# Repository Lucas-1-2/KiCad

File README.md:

# Raccolta di schematici e progettazioni PCB mediante KiCad

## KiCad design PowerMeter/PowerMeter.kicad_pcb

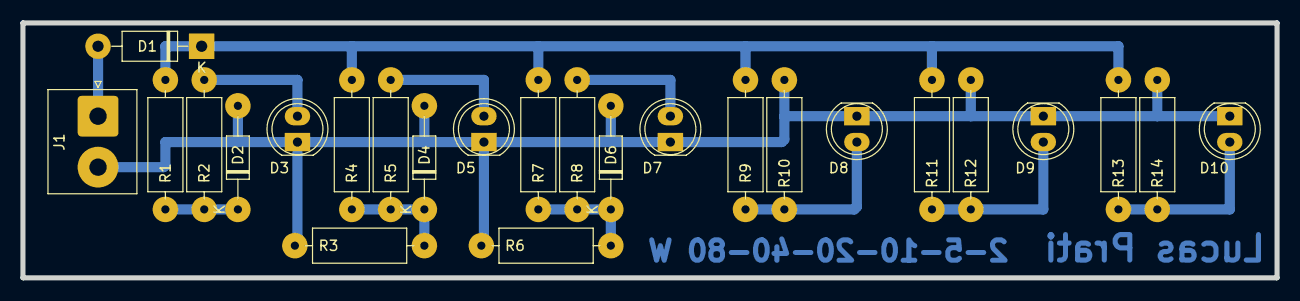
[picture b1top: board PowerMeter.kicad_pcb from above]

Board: 2 copper layers, 123.0 x 25.0 mm, 25 parts (0 on the bottom side), 12 nets.

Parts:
D1: 1N4004; D_DO-41_SOD81_P10.16mm_Horizontal
D2, D4, D6: 2,7V 500mW BZX79C2V7; D_DO-35_SOD27_P10.16mm_Horizontal
D3, D5, D7, D8, D9, D10: LED; LED_D5.0mm
J1: Conn_01x02_Male; JST_NV_B02P-NV_1x02_P5.00mm_Vertical
R1, R3: 220; R_Axial_DIN0309_L9.0mm_D3.2mm_P12.70mm_Horizontal
R2, R5, R6, R8, R10, R12, R14: 100; R_Axial_DIN0309_L9.0mm_D3.2mm_P12.70mm_Horizontal
R4, R7: 330; R_Axial_DIN0309_L9.0mm_D3.2mm_P12.70mm_Horizontal
R9: 560; R_Axial_DIN0309_L9.0mm_D3.2mm_P12.70mm_Horizontal
R11: 820; R_Axial_DIN0309_L9.0mm_D3.2mm_P12.70mm_Horizontal
R13: 1k2; R_Axial_DIN0309_L9.0mm_D3.2mm_P12.70mm_Horizontal

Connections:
GND: D2.2, D3.1, D4.2, D5.1, D6.2, D7.1, D8.1, D9.1, D10.1, J1.2, R3.2, R6.2, R10.2, R12.2, R14.2
unnamed: D1.1, R1.1, R4.1, R7.1, R9.1, R11.1, R13.1
unnamed: D2.1, R1.2, R2.2
unnamed: D3.2, R2.1
unnamed: D4.1, R3.1, R4.2, R5.2
unnamed: D5.2, R5.1
unnamed: D6.1, R6.1, R7.2, R8.2
unnamed: D7.2, R8.1
unnamed: D8.2, R9.2, R10.1
unnamed: D9.2, R11.2, R12.1
unnamed: D10.2, R13.2, R14.1
VCC: D1.2, J1.1

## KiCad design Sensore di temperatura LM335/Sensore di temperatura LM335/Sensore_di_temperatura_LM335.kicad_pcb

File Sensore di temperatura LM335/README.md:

# Progetto sensore di temperatura con LM335

**TPSEE; A.S. 2022/23, ITT G.Marconi - Forlì.**

- **Team**: Lucas Prati, Yassir El Kacimi
- **Docente**: prof. Samuele Mazzolini

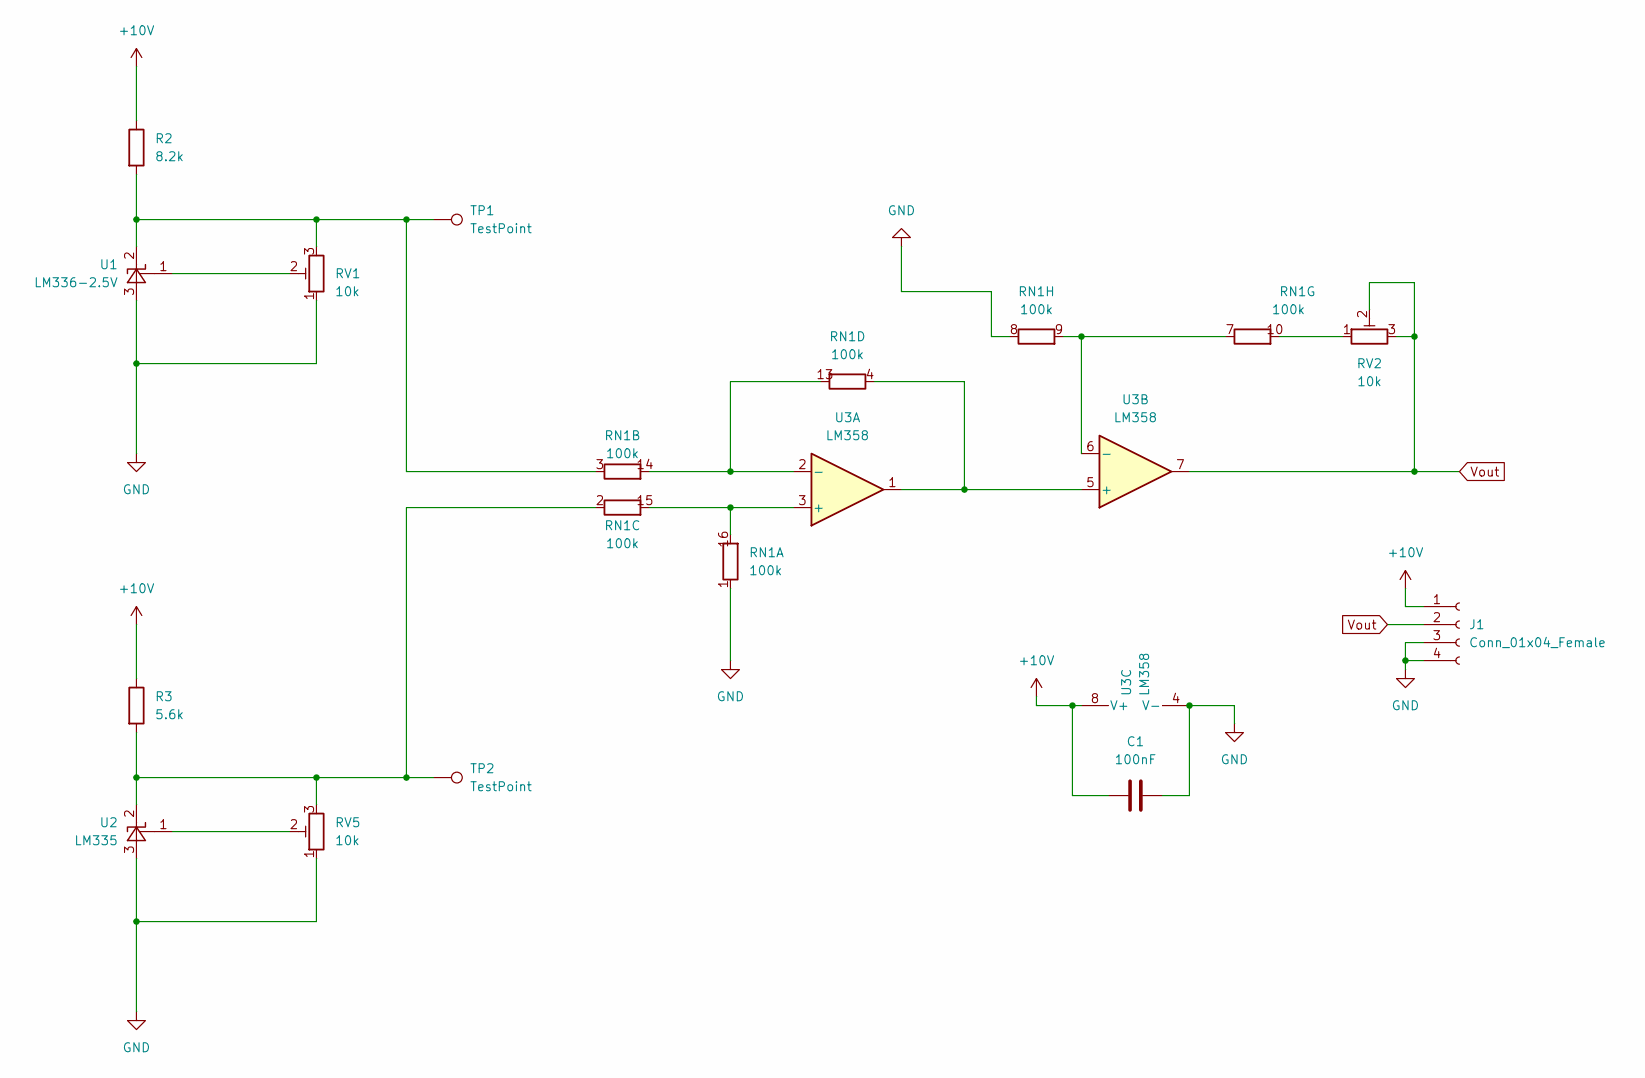
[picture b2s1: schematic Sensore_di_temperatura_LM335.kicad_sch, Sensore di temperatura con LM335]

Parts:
C1: 100nF; C_Rect_L7.0mm_W2.5mm_P5.00mm
J1: Conn_01x04_Female; TerminalBlock_Phoenix_MKDS-1,5-4_1x04_P5.00mm_Horizontal
R2: 8.2k; R_Axial_DIN0309_L9.0mm_D3.2mm_P12.70mm_Horizontal
R3: 5.6k; R_Axial_DIN0309_L9.0mm_D3.2mm_P12.70mm_Horizontal
RN1: 100k; DIP-16_W7.62mm_LongPads
RV1, RV2, RV5: 10k; Potentiometer_Bourns_3339P_Vertical
TP1, TP2: TestPoint; PinHeader_1x01_P2.00mm_Vertical
U1: LM336-2.5V; TO-92_Wide
U2: LM335; TO-92_Wide
U3: LM358; DIP-8_W7.62mm_LongPads

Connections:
+10V: C1.1, J1.1, R2.1, R3.1, U3.8 (V+)
GND: C1.2, J1.3, J1.4, RN1.1 (R1.1), RN1.8 (R8.1), RV1.1, RV5.1, U1.3 (A), U2.3 (A), U3.4 (V-)
unnamed: R2.2, RN1.3 (R3.1), RV1.3, TP1.1, U1.2 (K)
unnamed: R3.2, RN1.2 (R2.1), RV5.3, TP2.1, U2.2 (K)
unnamed: RN1.4 (R4.1), U3.1, U3.5 (+)
unnamed: RN1.7 (R7.1), RN1.9 (R8.2), U3.6 (-)
unnamed: RN1.10 (R7.2), RV2.1
unnamed: RN1.13 (R4.2), RN1.14 (R3.2), U3.2 (-)
unnamed: RN1.15 (R2.2), RN1.16 (R1.2), U3.3 (+)
unnamed: RV1.2, U1.1 (FB)
unnamed: RV5.2, U2.1 (FB)
Vout: J1.2, RV2.2, RV2.3, U3.7

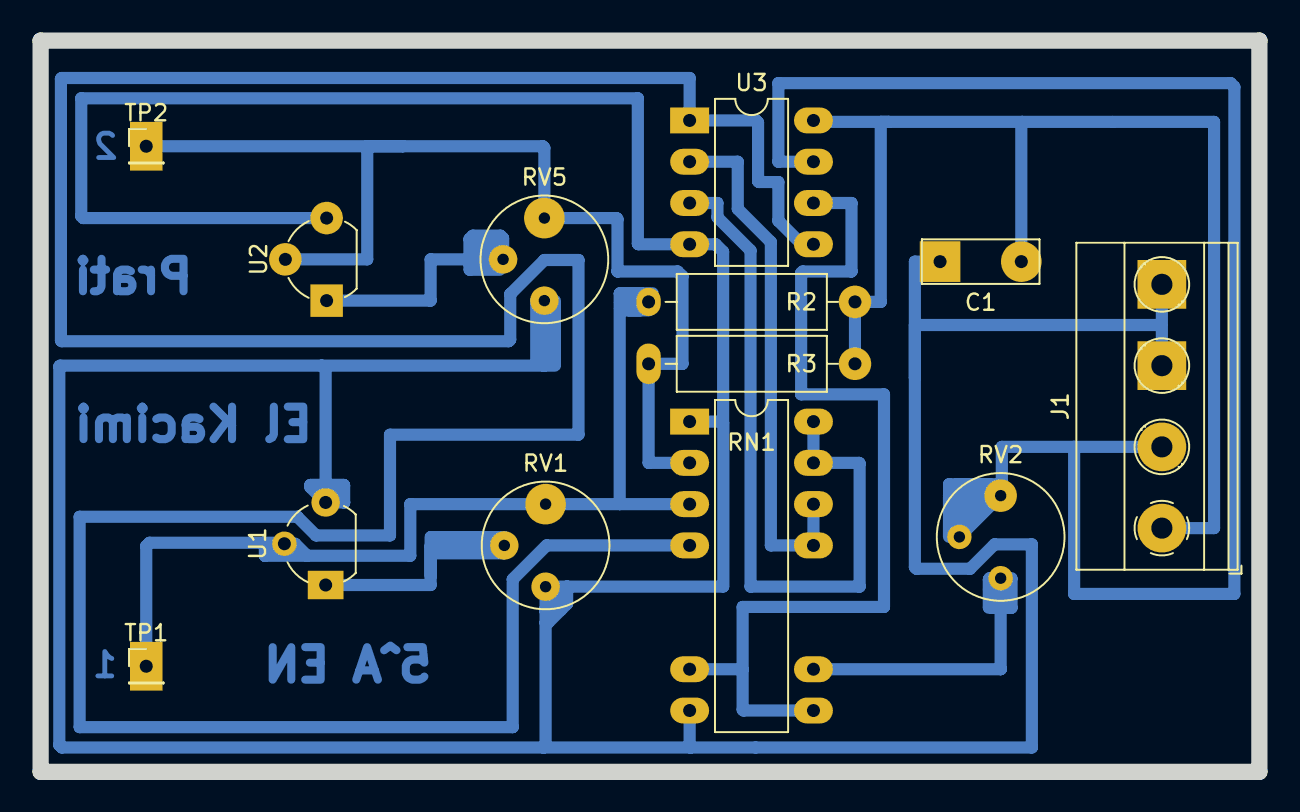
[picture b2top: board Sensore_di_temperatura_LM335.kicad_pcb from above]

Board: 2 copper layers, 75.0 x 45.0 mm, 13 parts (0 on the bottom side), 12 nets.

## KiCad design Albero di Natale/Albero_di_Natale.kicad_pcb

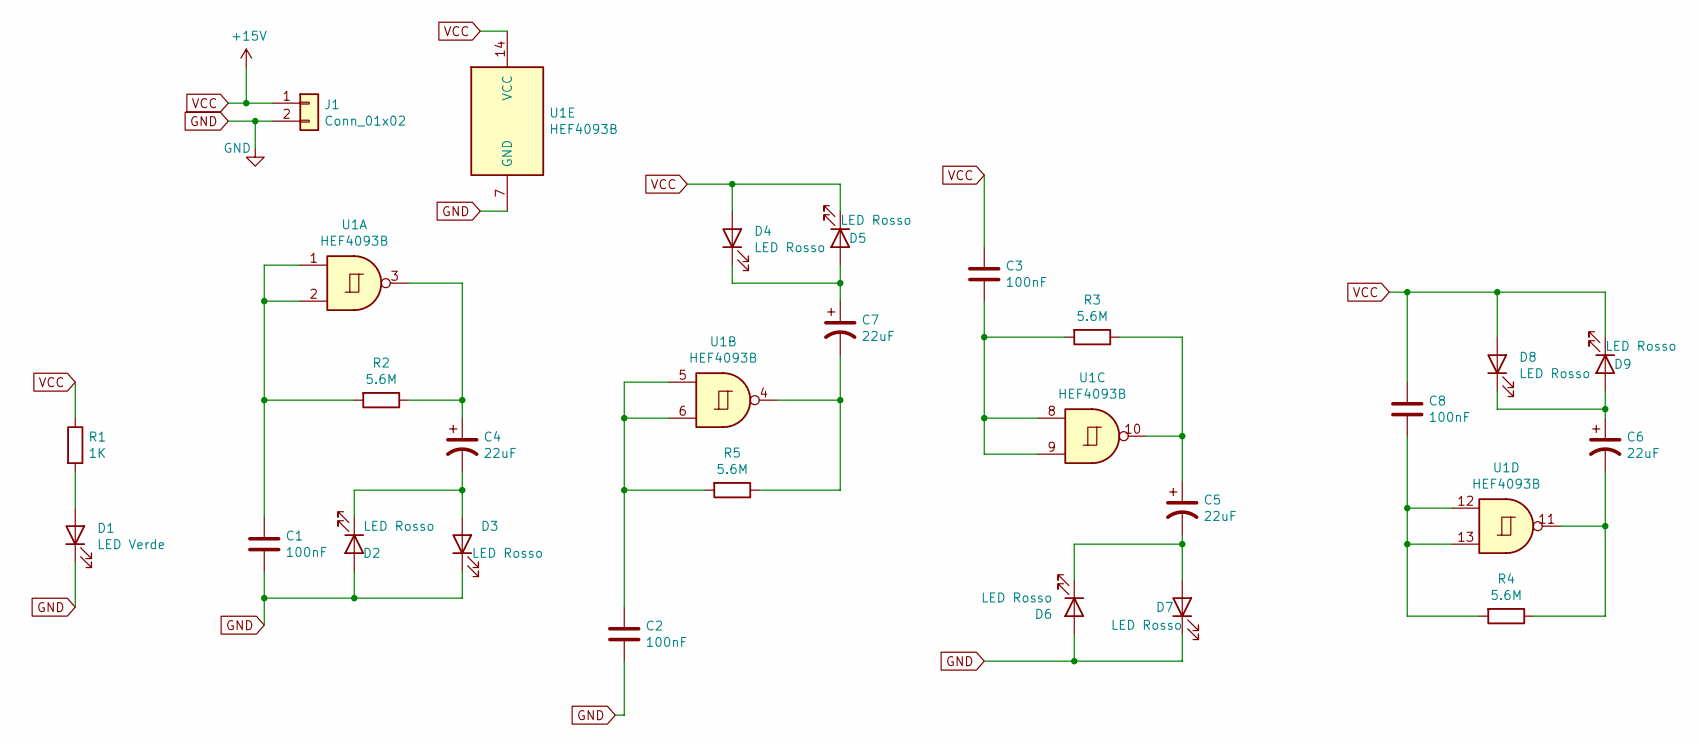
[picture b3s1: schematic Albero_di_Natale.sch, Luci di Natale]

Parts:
C1, C2, C3, C8: 100nF; C_Disc_D3.8mm_W2.6mm_P2.50mm
C4, C5, C6, C7: 22uF; C_Radial_D6.3mm_H5.0mm_P2.50mm
D1: LED Verde; LED_D5.0mm
D2, D3, D4, D5, D6, D7, D8, D9: LED Rosso; LED_D5.0mm
J1: Conn_01x02; JST_NV_B02P-NV_1x02_P5.00mm_Vertical
R1: 1K; R_Axial_DIN0309_L9.0mm_D3.2mm_P12.70mm_Horizontal
R2, R3, R4, R5: 5.6M; R_Axial_DIN0309_L9.0mm_D3.2mm_P12.70mm_Horizontal
U1: HEF4093B; DIP-14_W7.62mm_LongPads

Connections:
GND: C1.2, C2.2, D1.1 (K), D2.2 (A), D3.1 (K), D6.2 (A), D7.1 (K), J1.2, U1.7 (GND)
unnamed: C1.1, R2.2, U1.1, U1.2
unnamed: C2.1, R5.2, U1.5, U1.6
unnamed: C3.2, R3.2, U1.8, U1.9
unnamed: C4.1, R2.1, U1.3
unnamed: C4.2, D2.1 (K), D3.2 (A)
unnamed: C5.1, R3.1, U1.10
unnamed: C5.2, D6.1 (K), D7.2 (A)
unnamed: C6.1, D8.1 (K), D9.2 (A)
unnamed: C6.2, R4.1, U1.11
unnamed: C7.1, D4.1 (K), D5.2 (A)
unnamed: C7.2, R5.1, U1.4
unnamed: C8.2, R4.2, U1.12, U1.13
unnamed: D1.2 (A), R1.2
VCC: C3.1, C8.1, D4.2 (A), D5.1 (K), D8.2 (A), D9.1 (K), J1.1, R1.1, U1.14 (VCC)

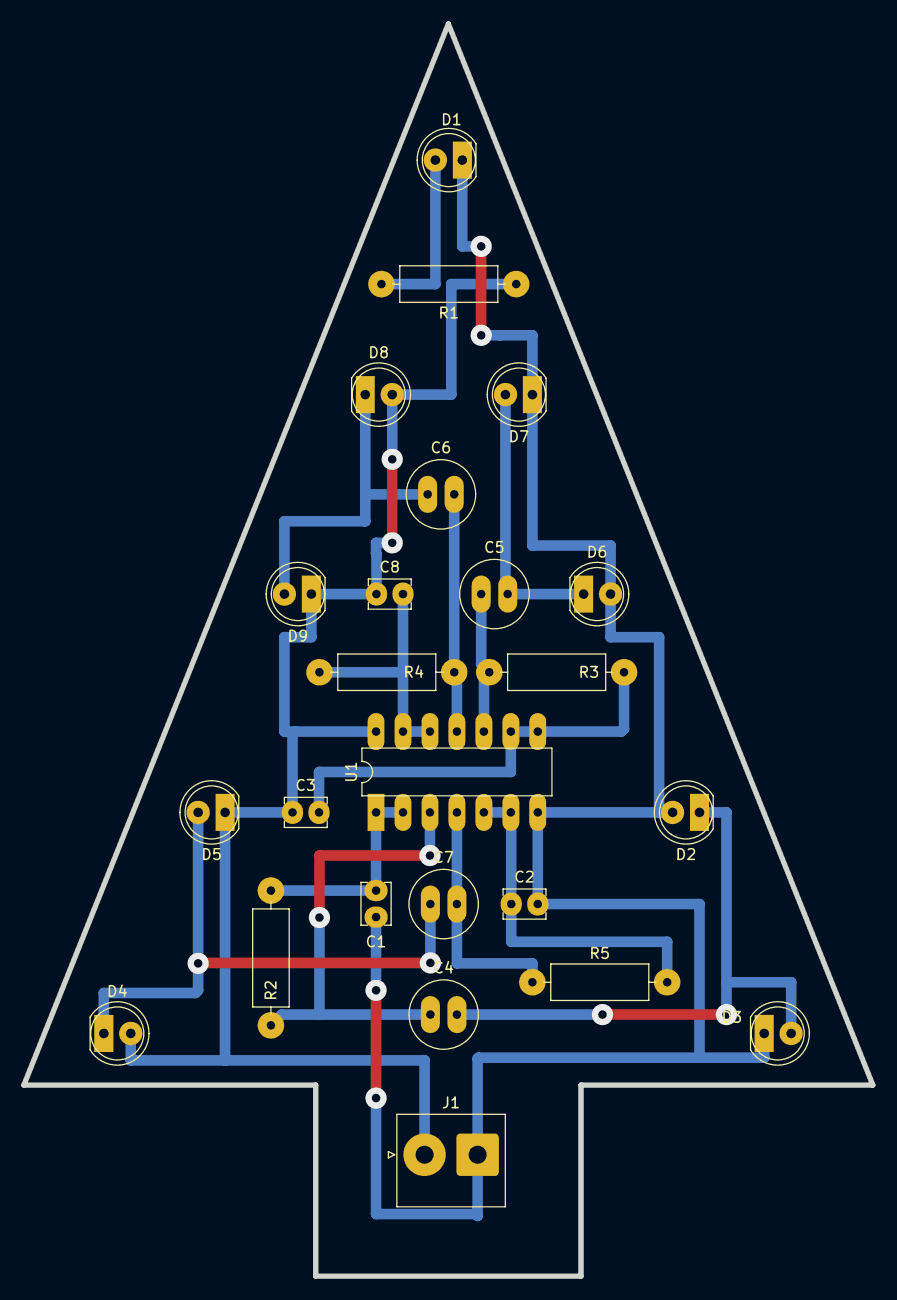
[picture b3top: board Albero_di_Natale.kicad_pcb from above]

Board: 2 copper layers, 80.0 x 118.0 mm, 24 parts (0 on the bottom side), 15 nets.

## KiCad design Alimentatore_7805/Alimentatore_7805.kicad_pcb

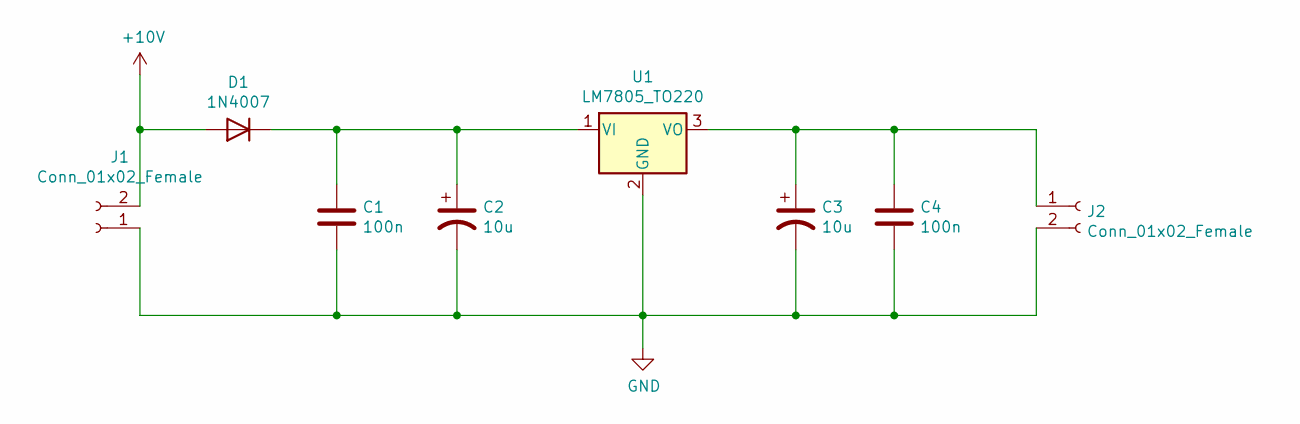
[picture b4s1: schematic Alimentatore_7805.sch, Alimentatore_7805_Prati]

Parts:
C1, C4: 100n; C_Disc_D3.8mm_W2.6mm_P2.50mm
C2, C3: 10u; C_Radial_D6.3mm_H5.0mm_P2.50mm
D1: 1N4007; D_DO-41_SOD81_P10.16mm_Horizontal
J1, J2: Conn_01x02_Female; JST_NV_B02P-NV_1x02_P5.00mm_Vertical
U1: LM7805_TO220; TO-220-3_Vertical

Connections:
+10V: D1.2 (A), J1.2
GND: C1.2, C2.2, C3.2, C4.2, J1.1, J2.2, U1.2 (GND)
unnamed: C1.1, C2.1, D1.1 (K), U1.1 (VI)
unnamed: C3.1, C4.1, J2.1, U1.3 (VO)

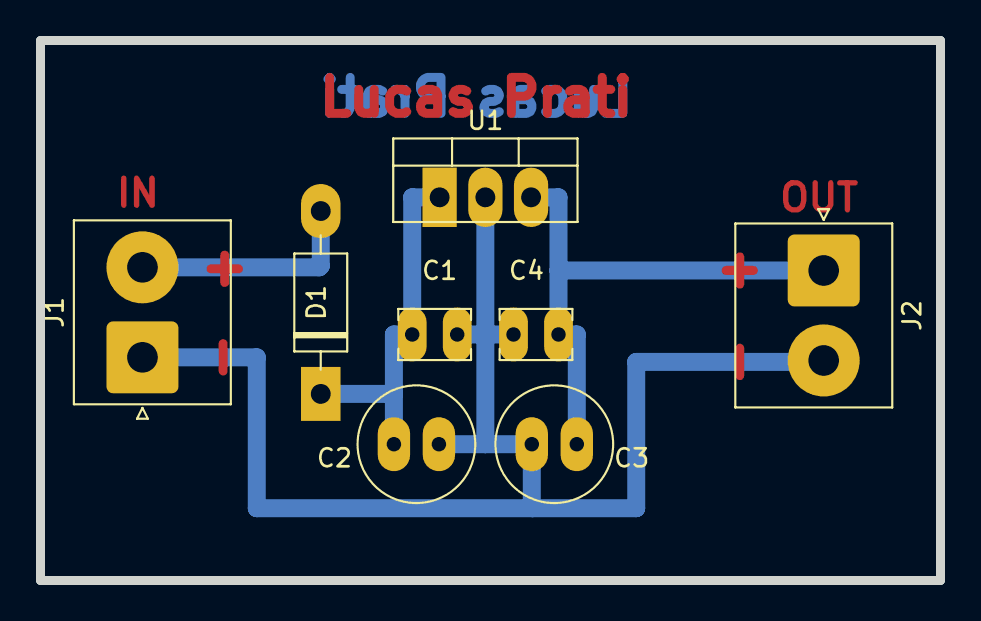
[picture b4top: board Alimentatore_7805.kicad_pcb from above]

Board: 2 copper layers, 50.0 x 30.0 mm, 8 parts (0 on the bottom side), 4 nets.

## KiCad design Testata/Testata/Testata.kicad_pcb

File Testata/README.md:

# Progetto Illuminazione Testata Letto

Il progetto si pone come obbiettivo la modellazione di un PCB per una scheda Arduino Nano e per il relativo circuito di gestione di un sistema di illuminazione led RGB con sensore di prossimità e luminosità esterno

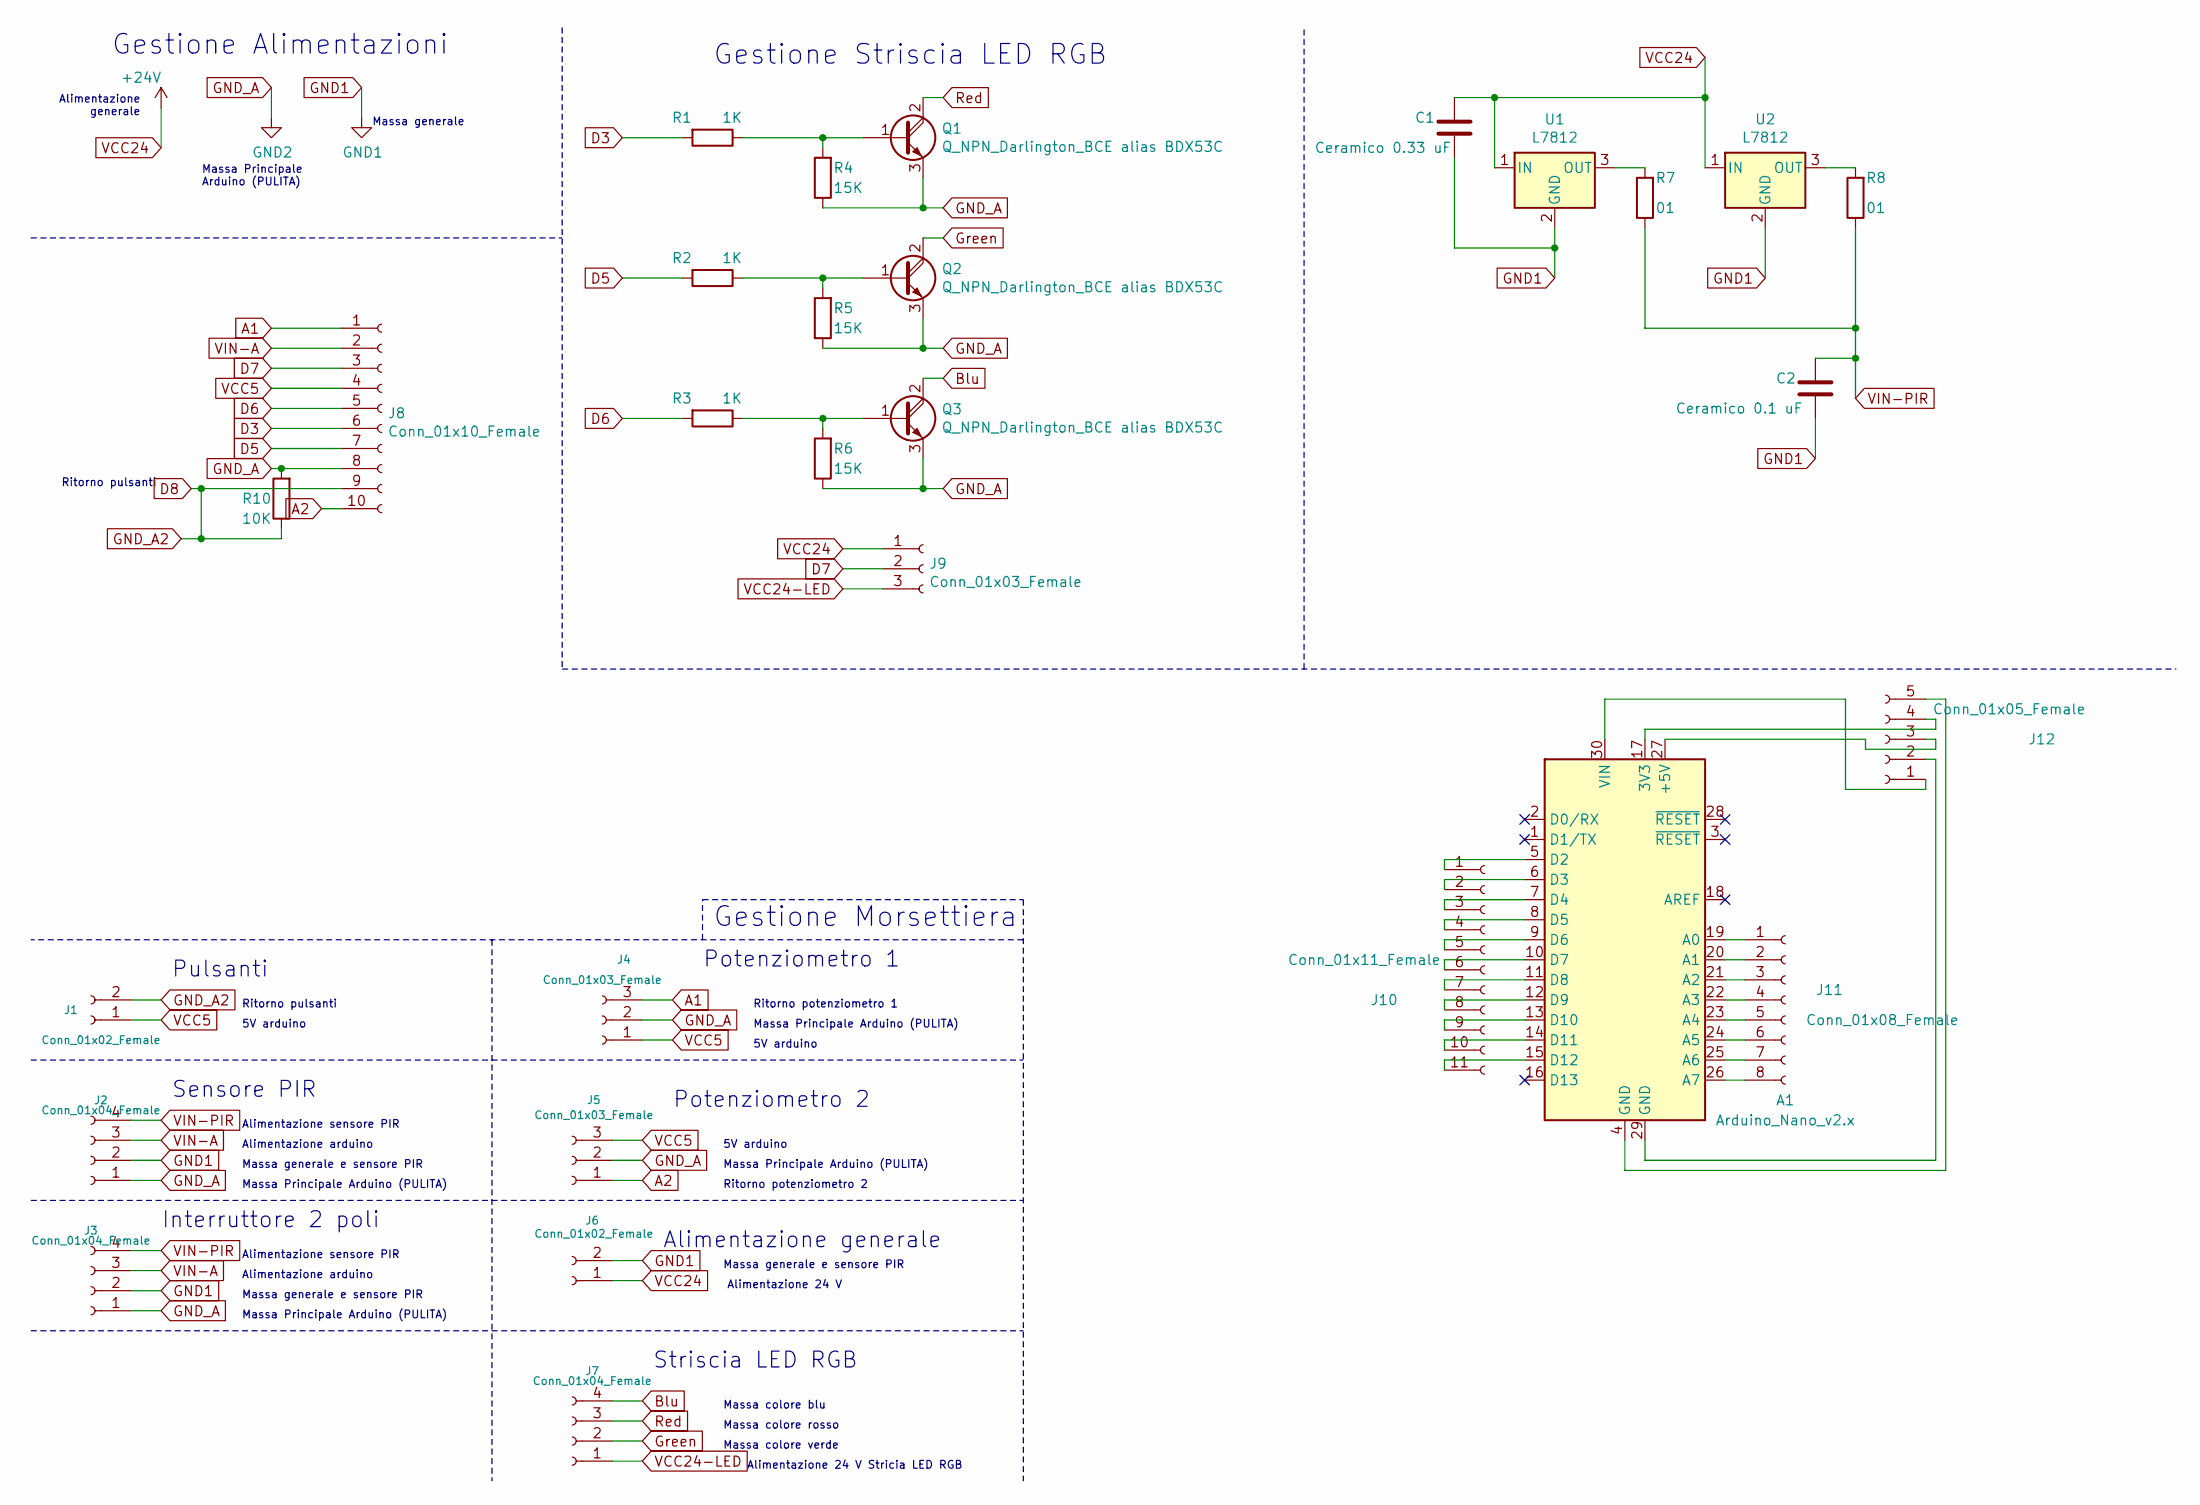
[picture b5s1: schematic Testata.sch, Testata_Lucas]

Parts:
A1: Arduino_Nano_v2.x; Arduino_Nano
C1: Ceramico 0.33 uF; C_Disc_D3.8mm_W2.6mm_P2.50mm
C2: Ceramico 0.1 uF; C_Disc_D3.8mm_W2.6mm_P2.50mm
J1, J6: Conn_01x02_Female; PhoenixContact_MSTBA_2,5_2-G-5,08_1x02_P5.08mm_Horizontal
J2, J3, J7: Conn_01x04_Female; PhoenixContact_MSTBA_2,5_4-G-5,08_1x04_P5.08mm_Horizontal
J4, J5, J9: Conn_01x03_Female; PhoenixContact_MSTBA_2,5_3-G-5,08_1x03_P5.08mm_Horizontal
J8: Conn_01x10_Female; PhoenixContact_MSTBA_2,5_10-G-5,08_1x10_P5.08mm_Horizontal
J10: Conn_01x11_Female; PhoenixContact_MSTBA_2,5_11-G-5,08_1x11_P5.08mm_Horizontal
J11: Conn_01x08_Female; PhoenixContact_MSTBA_2,5_8-G-5,08_1x08_P5.08mm_Horizontal
J12: Conn_01x05_Female; PhoenixContact_MSTBA_2,5_5-G-5,08_1x05_P5.08mm_Horizontal
Q1, Q2, Q3: Q_NPN_Darlington_BCE alias BDX53C; TO-220-3_Vertical
R1, R2, R3: 1K; R_Axial_DIN0309_L9.0mm_D3.2mm_P12.70mm_Horizontal
R4, R5, R6: 15K; R_Axial_DIN0309_L9.0mm_D3.2mm_P12.70mm_Horizontal
R7, R8: 01; R_Axial_DIN0309_L9.0mm_D3.2mm_P12.70mm_Horizontal
R10: 10K; R_Axial_DIN0309_L9.0mm_D3.2mm_P12.70mm_Horizontal
U1, U2: L7812; TO-220-3_Vertical

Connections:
A1: J4.3, J8.1
A2: J5.1, J8.10
Blu: J7.4, Q3.2 (C)
D3: J8.6, R1.2
D5: J8.7, R2.2
D6: J8.5, R3.2
D7: J8.3, J9.2
D8: J1.2, J8.9, R10.1
GND1: C1.2, C2.2, J2.2, J3.2, J6.2, U1.2 (GND), U2.2 (GND)
GND_A: J2.1, J3.1, J4.2, J5.2, J8.8, Q1.3 (E), Q2.3 (E), Q3.3 (E), R4.1, R5.1, R6.1, R10.2
Green: J7.2, Q2.2 (C)
unnamed: A1.4 (GND), J12.5
unnamed: A1.5 (D2), J10.1
unnamed: A1.6 (D3), J10.2
unnamed: A1.7 (D4), J10.3
unnamed: A1.8 (D5), J10.4
unnamed: A1.9 (D6), J10.5
unnamed: A1.10 (D7), J10.6
unnamed: A1.11 (D8), J10.7
unnamed: A1.12 (D9), J10.8
unnamed: A1.13 (D10), J10.9
unnamed: A1.14 (D11), J10.10
unnamed: A1.15 (D12), J10.11
unnamed: A1.17 (3V3), J12.4
unnamed: A1.19 (A0), J11.1
unnamed: A1.20 (A1), J11.2
unnamed: A1.21 (A2), J11.3
unnamed: A1.22 (A3), J11.4
unnamed: A1.23 (A4), J11.5
unnamed: A1.24 (A5), J11.6
unnamed: A1.25 (A6), J11.7
unnamed: A1.26 (A7), J11.8
unnamed: A1.27 (+5V), J12.3
unnamed: A1.29 (GND), J12.2
unnamed: A1.30 (VIN), J12.1
unnamed: Q1.1 (B), R1.1, R4.2
unnamed: Q2.1 (B), R2.1, R5.2
unnamed: Q3.1 (B), R3.1, R6.2
unnamed: R7.2, U1.3 (OUT)
unnamed: R8.2, U2.3 (OUT)
Red: J7.3, Q1.2 (C)
VCC5: J1.1, J4.1, J5.3, J8.4
VCC24: C1.1, J6.1, J9.1, U1.1 (IN), U2.1 (IN)
VCC24-LED: J7.1, J9.3
VIN-A: J2.3, J3.3, J8.2
VIN-PIR: C2.1, J2.4, J3.4, R7.1, R8.1

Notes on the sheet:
Massa generale
Alimentazione generale
Gestione Striscia LED RGB
Massa Principale Arduino (PULITA)
Gestione Alimentazioni
Ritorno pulsanti
5V arduino
Alimentazione sensore PIR
Alimentazione arduino
Massa generale e sensore PIR
Massa Principale Arduino (PULITA)
Ritorno potenziometro 1
Ritorno potenziometro 2
Alimentazione 24 V
Massa colore blu
Massa colore rosso
Alimentazione 24 V Stricia LED RGB
Pulsanti
Interruttore 2 poli
Potenziometro 2
Alimentazione generale
Striscia LED RGB
Potenziometro 1
Sensore PIR
Gestione Morsettiera
Massa colore verde

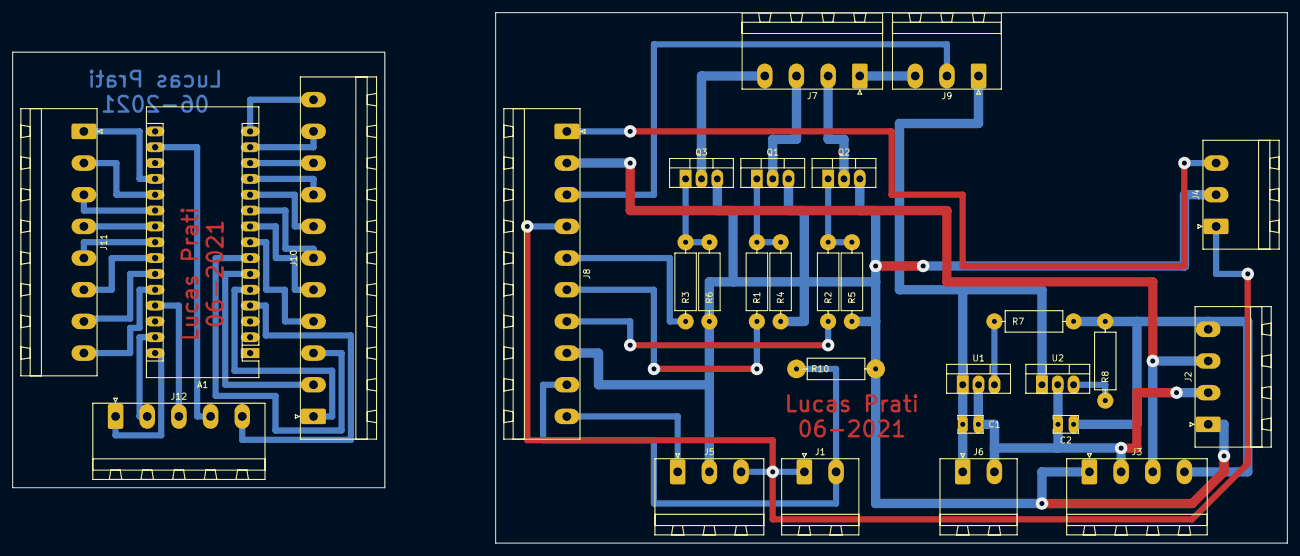
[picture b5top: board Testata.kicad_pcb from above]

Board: 2 copper layers, 127.0 x 85.1 mm, 29 parts (0 on the bottom side), 46 nets.

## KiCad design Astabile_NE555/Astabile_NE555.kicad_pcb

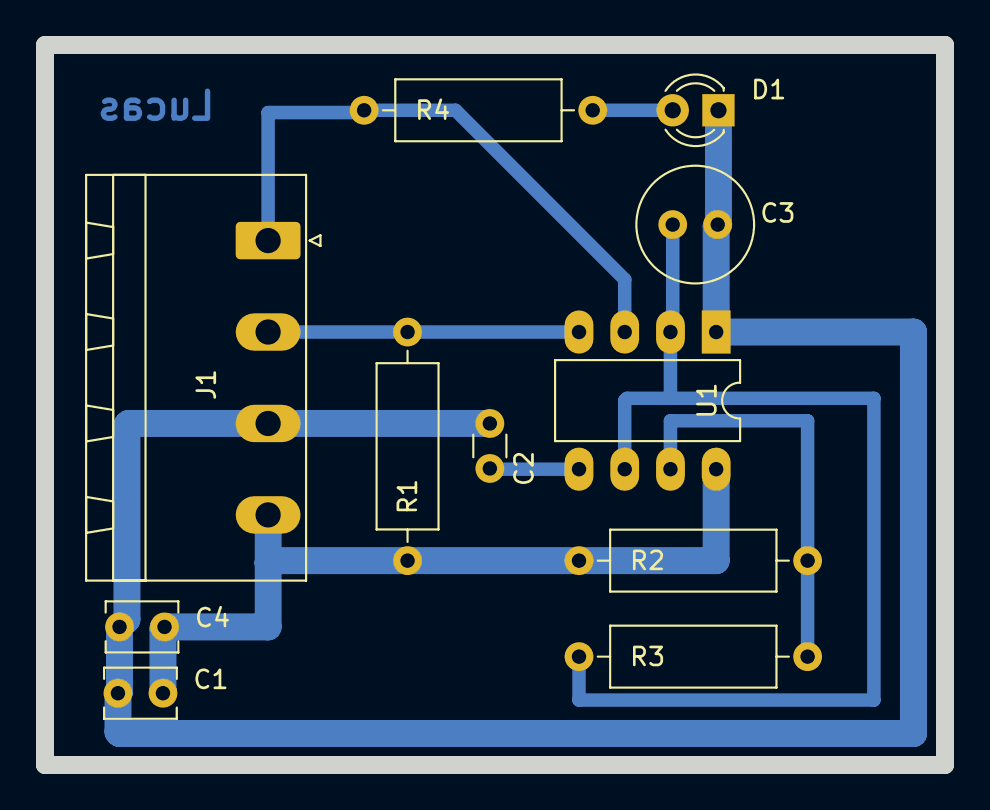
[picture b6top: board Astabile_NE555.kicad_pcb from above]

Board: 2 copper layers, 50.0 x 40.0 mm, 11 parts (0 on the bottom side), 8 nets.

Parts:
C1, C4: 100n; C_Disc_D3.8mm_W2.6mm_P2.50mm
C2: 10n; C_Disc_D3.0mm_W1.6mm_P2.50mm
C3: 2u2; C_Radial_D6.3mm_H5.0mm_P2.50mm
D1: LED; LED_D3.0mm
J1: Conn_01x04_Female; PhoenixContact_MSTBA_2,5_4-G-5,08_1x04_P5.08mm_Horizontal
R1: 10k; R_Axial_DIN0309_L9.0mm_D3.2mm_P12.70mm_Horizontal
R2: 33k; R_Axial_DIN0309_L9.0mm_D3.2mm_P12.70mm_Horizontal
R3: 330k; R_Axial_DIN0309_L9.0mm_D3.2mm_P12.70mm_Horizontal
R4: 330; R_Axial_DIN0309_L9.0mm_D3.2mm_P12.70mm_Horizontal
U1: NE555P; DIP-8_W7.62mm_LongPads

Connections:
+5V: C1.1, C4.1, J1.4, R1.1, R2.1, U1.8
ENABLE: J1.2, R1.2, U1.4
GND: C1.2, C2.2, C3.2, C4.2, D1.1, J1.3, U1.1
unnamed: C2.1, U1.5
unnamed: C3.1, R3.2, U1.2, U1.6
unnamed: D1.2, R4.2
unnamed: R2.2, R3.1, U1.7
OUT: J1.1, R4.1, U1.3

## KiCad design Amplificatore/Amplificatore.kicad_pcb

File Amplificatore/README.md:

# Progetto amplificatore audio

**TPSEE; A.S. 2021/22, ITT G.Marconi - Forlì.**

- **Docente**: prof. Samuele Mazzolini.

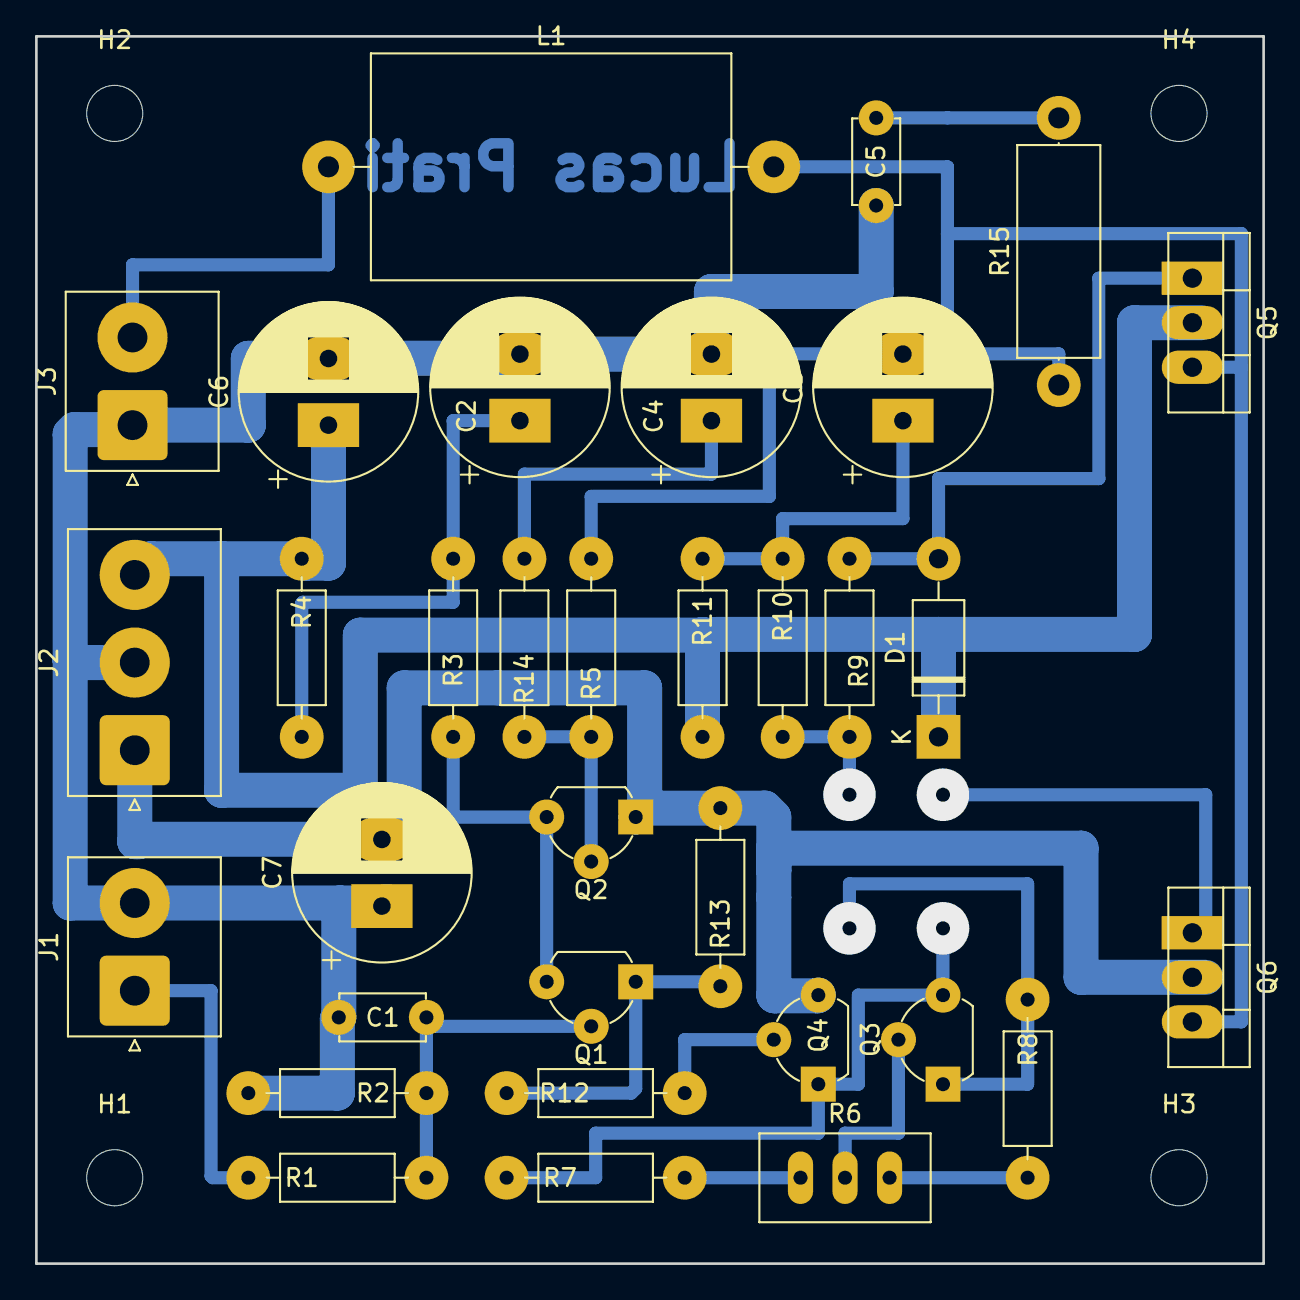
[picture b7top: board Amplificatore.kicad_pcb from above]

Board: 2 copper layers, 70.0 x 70.0 mm, 37 parts (0 on the bottom side), 21 nets.

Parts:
C1: 220pF; C_Disc_D4.7mm_W2.5mm_P5.00mm
C2, C3: 47uF; CP_Radial_D10.0mm_P3.80mm
C4, C6, C7: 100uF; CP_Radial_D10.0mm_P3.80mm
C5: 68nF; C_Disc_D4.7mm_W2.5mm_P5.00mm
D1: 1N4002; D_DO-41_SOD81_P10.16mm_Horizontal
H1, H2, H3, H4: MountingHole; MountingHole_3.2mm_M3
J1: INPUT; JST_NV_B02P-NV_1x02_P5.00mm_Vertical
J2: Alimentazione; JST_NV_B03P-NV_1x03_P5.00mm_Vertical
J3: OUTPUT; JST_NV_B02P-NV_1x02_P5.00mm_Vertical
L1: *; L_Axial_L20.3mm_D12.7mm_P25.40mm_Horizontal_Vishay_IHA-201
Q1, Q2: BC556; TO-92L_Wide
Q3, Q4: BC546; TO-92L_Wide
Q5: IRF540N; TO-220-3_Vertical
Q6: IRF9540N; TO-220-3_Vertical
R1, R12: 4.7k; R_Axial_DIN0207_L6.3mm_D2.5mm_P10.16mm_Horizontal
R2, R5: 47k; R_Axial_DIN0207_L6.3mm_D2.5mm_P10.16mm_Horizontal
R3: 15k; R_Axial_DIN0207_L6.3mm_D2.5mm_P10.16mm_Horizontal
R4: 1.2k; R_Axial_DIN0207_L6.3mm_D2.5mm_P10.16mm_Horizontal
R6: 1k; Potentiometer_Bourns_3296W_Vertical
R7: 820; R_Axial_DIN0207_L6.3mm_D2.5mm_P10.16mm_Horizontal
R8: 10k; R_Axial_DIN0207_L6.3mm_D2.5mm_P10.16mm_Horizontal
R9: 680ohm; R_Axial_DIN0207_L6.3mm_D2.5mm_P10.16mm_Horizontal
R10, R11: 2.7k; R_Axial_DIN0207_L6.3mm_D2.5mm_P10.16mm_Horizontal
R13: 560; R_Axial_DIN0207_L6.3mm_D2.5mm_P10.16mm_Horizontal
R14: 2.2k; R_Axial_DIN0207_L6.3mm_D2.5mm_P10.16mm_Horizontal
R15: 10ohm/2W; R_Axial_DIN0414_L11.9mm_D4.5mm_P15.24mm_Horizontal

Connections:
+35: C6.1, D1.1, J2.3, Q5.2, R4.1, R11.1
-35: C7.2, J2.1, Q2.1, Q4.3, Q6.2, R13.2
GND: C1.2, C2.2, C4.2, C5.2, C6.2, C7.1, J1.2, J2.2, J3.1, R2.2
unnamed: C1.1, Q1.2, R1.1, R2.1
unnamed: C2.1, R3.1, R4.2
unnamed: C3.1, R10.1, R11.2
unnamed: C3.2, L1.2, Q5.3, Q6.3, R5.1, R15.1
unnamed: C4.1, R14.2
unnamed: C5.1, R15.2
unnamed: D1.2, Q5.1, R9.1
unnamed: J1.1, R1.2
unnamed: J3.2, L1.1
unnamed: Q1.1, R12.2, R13.1
unnamed: Q1.3, Q2.3, R3.2
unnamed: Q2.2, R5.2, R14.1
unnamed: Q3.1, R8.1, R9.2, R10.2
unnamed: Q3.2, R6.2
unnamed: Q3.3, Q4.1, Q6.1, R7.1
unnamed: Q4.2, R12.1
unnamed: R6.1, R8.2
unnamed: R6.3, R7.2

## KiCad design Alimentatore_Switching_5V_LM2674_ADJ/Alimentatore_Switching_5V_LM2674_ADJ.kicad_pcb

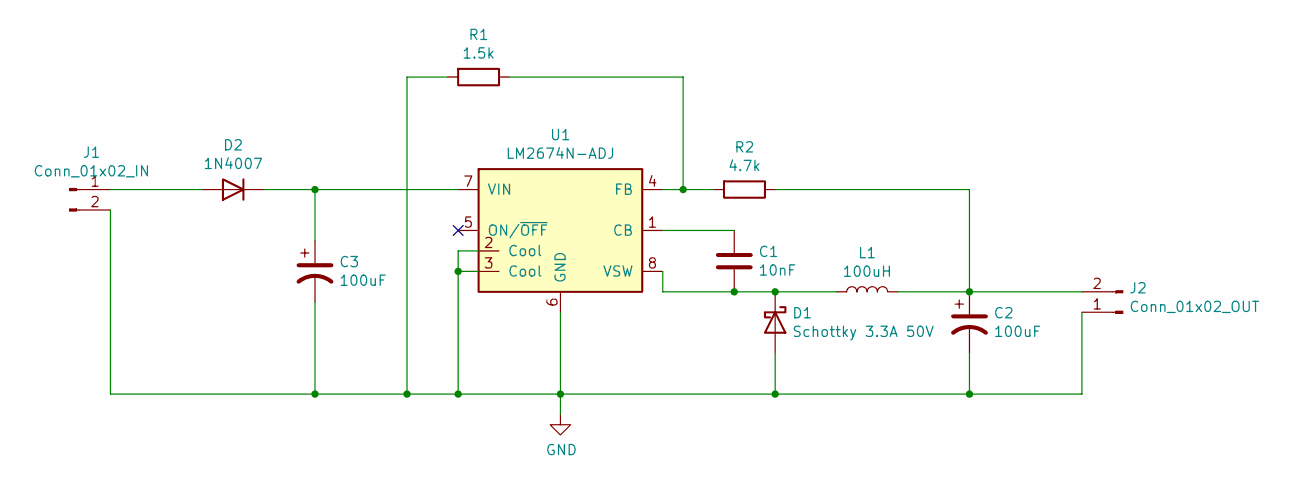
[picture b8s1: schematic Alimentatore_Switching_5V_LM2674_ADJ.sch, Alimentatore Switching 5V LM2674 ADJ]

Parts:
C1: 10nF; C_Disc_D3.8mm_W2.6mm_P2.50mm
C2, C3: 100uF; C_Radial_D6.3mm_H5.0mm_P2.50mm
D1: Schottky 3.3A 50V; D_DO-41_SOD81_P10.16mm_Horizontal
D2: 1N4007; D_DO-41_SOD81_P10.16mm_Horizontal
J1: Conn_01x02_IN; JST_NV_B02P-NV_1x02_P5.00mm_Vertical
J2: Conn_01x02_OUT; JST_NV_B02P-NV_1x02_P5.00mm_Vertical
L1: 100uH; L_Toroid_Vertical_L13.0mm_W6.5mm_P5.60mm
R1: 1.5k; R_Axial_DIN0309_L9.0mm_D3.2mm_P12.70mm_Horizontal
R2: 4.7k; R_Axial_DIN0309_L9.0mm_D3.2mm_P12.70mm_Horizontal
U1: LM2674N-ADJ; DIP-8_W7.62mm

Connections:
GND: C2.2, C3.2, D1.2 (A), J1.2, J2.1, R1.2, U1.2 (Cool), U1.3 (Cool), U1.6 (GND)
unnamed: C1.1, D1.1 (K), L1.1, U1.8 (VSW)
unnamed: C1.2, U1.1 (CB)
unnamed: C2.1, J2.2, L1.2, R2.1
unnamed: C3.1, D2.1 (K), U1.7 (VIN)
unnamed: D2.2 (A), J1.1
unnamed: R1.1, R2.2, U1.4 (FB)

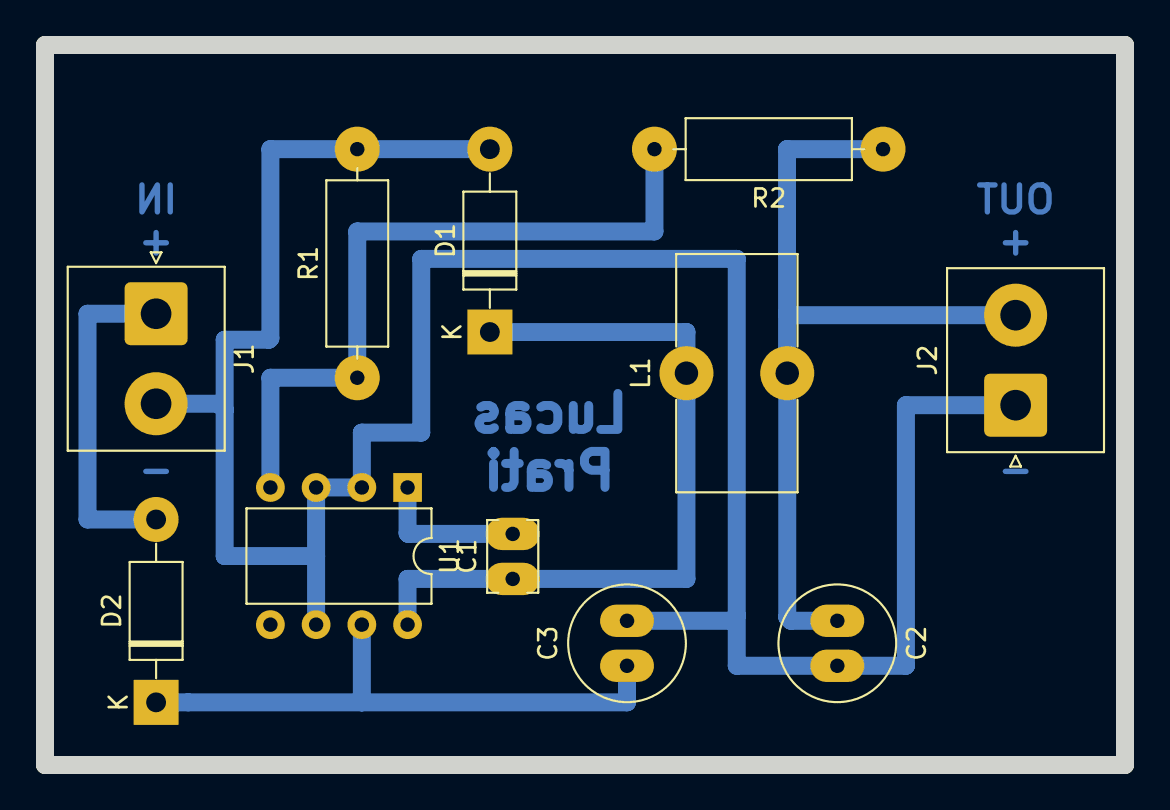
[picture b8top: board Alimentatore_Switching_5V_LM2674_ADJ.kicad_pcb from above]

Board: 2 copper layers, 60.0 x 40.0 mm, 11 parts (0 on the bottom side), 7 nets.

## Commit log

2025-03-13 Uploading personal and extracurricular projects
2025-03-14 Upload ne555, barra led, contatore UP
2025-03-14 Improve directory organization
2025-03-14 Upload projects
